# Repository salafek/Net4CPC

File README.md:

# Net4CPC
Net4CPC is an Ethernet interface for the [Amstrad CPC](https://www.cpcwiki.eu/index.php/CPC) range of computers.</br>
It is a stand alone implemetation of the Ethernet interface found on the [Cyboard](https://github.com/salafek/cyboard-for-cpc).</br>
It is supported by [SymbOS](http://symbos.de) and by [KCNet utilities](https://github.com/salafek/KCNet-software-for-Net4CPC) for CP/M.</br> 
</br>

## Notes
The interface has a [Mother X4](https://cpcrulez.fr/hardware-interface-mother_x4.htm) compatible connector.</br> 
The network module is based on the [WIZnet's W5100S](https://www.wiznet.io/product-item/w5100s/) embedded ethernet controller and works in indirect parallel bus mode.</br>
In this mode it needs 4 I/O ports:
- #FD20: MR - Common Register MR
- #FD21: IDM_ARH - Upper 8 bits Offset Address Register
- #FD22: IDM_ARL - Lower 8 bits Offset Address Register
- #FD23: IDM_DR - 8 Bits Data Register

A detailed description on how to program the module, with flow diagrams and programming examples, can be found at the WIZnet's official site:</br>
[W5100S TCP Function](https://docs.wiznet.io/Product/iEthernet/W5100S/Application-Note/tcp)</br>
[W5100S UDP Function](https://docs.wiznet.io/Product/iEthernet/W5100S/Application-Note/udp)</br>
[SOCKET-less Command](https://docs.wiznet.io/Product/iEthernet/W5100S/Application-Note/socket-less-command)</br>

The PCB has provision for 2 differrent types of Ethernet modules:
- A Chinese [W5100S module](https://www.aliexpress.com/w/wholesale-%22W5100S-Network-Module%22-parallel.html?catId=0&initiative_id=SB_20230206005326&SearchText=%22W5100S%20Network%20Module%22%20parallel&spm=a2g0o.productlist.1000002.0) with an integrated 3.3V regulator.</br> 
- The original WIZnet's [W5100S](https://github.com/Wiznet/Hardware-Files-of-WIZnet/tree/master/05_Network_Module/WIZ810SMJ) or [W6100](https://github.com/Wiznet/Hardware-Files-of-WIZnet/tree/master/05_Network_Module/WIZ610MJ) modules.</br> 
## Build info
The schematic and layout were generated with Autodesk EAGLE 9.6.2 free edition</br>

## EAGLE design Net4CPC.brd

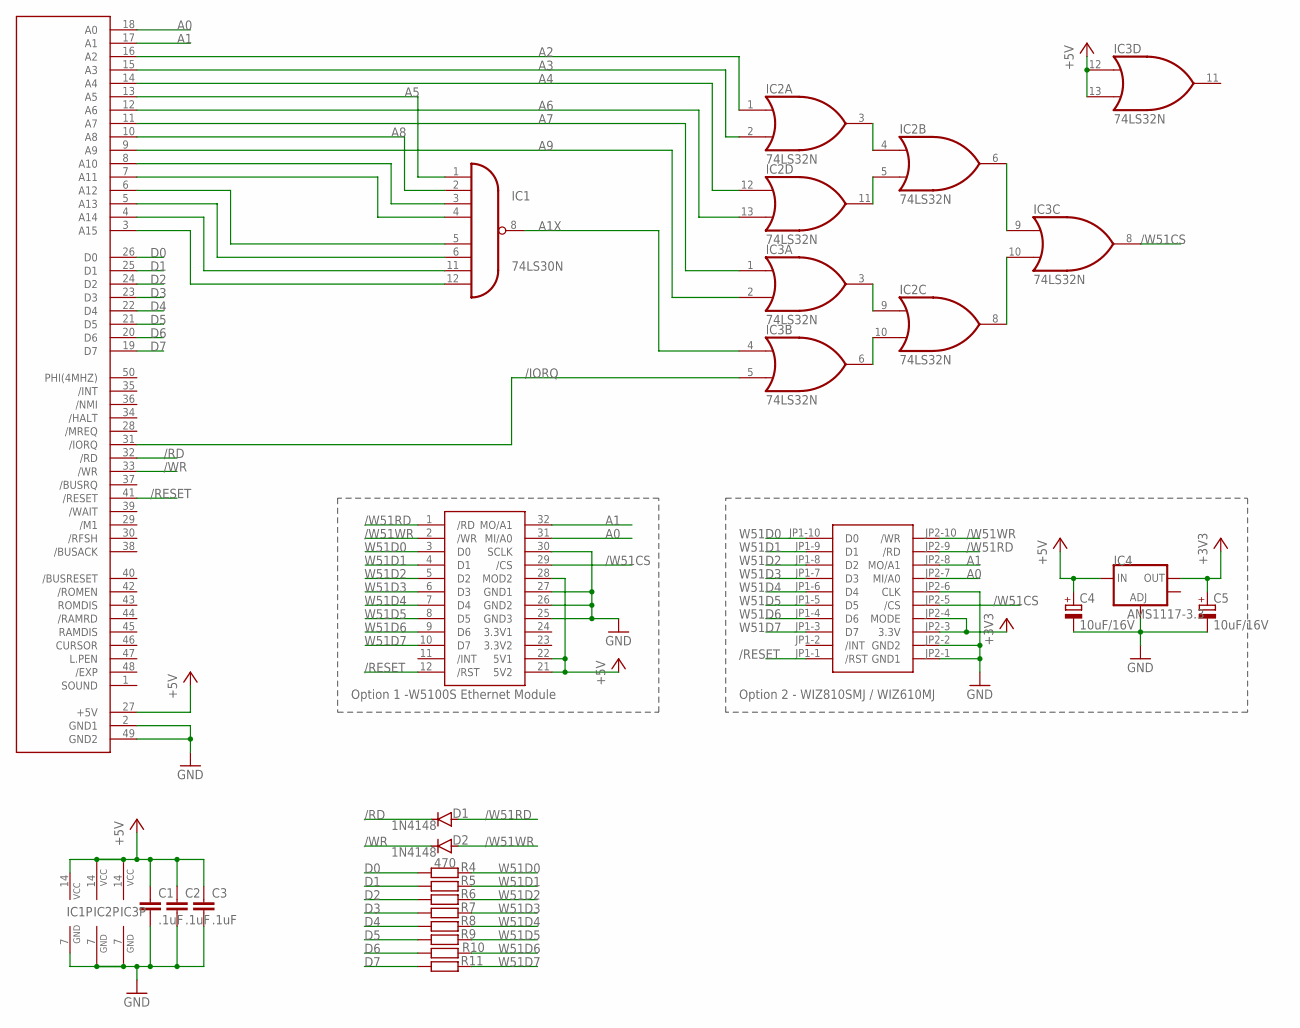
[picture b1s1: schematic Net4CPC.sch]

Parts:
C1, C2, C3: .1uF; C025-025X050
C4, C5: 10uF/16V; E5-6
CON1: CPCBUS; 2X25
D1, D2: 1N4148; DO35-7
IC1: 74LS30N; DIL14
IC2, IC3: 74LS32N; DIL14
IC4: AMS1117-3.3; SOT223
R4, R5, R6, R7, R8, R9, R10, R11: 470; 0204/7
W5100S-MODULE: W5100S-NETWORK-MODULENO-NAMES; W5100S-NETWORK-MODULE-NO-NAMES
WIZ810SMJ: WIZ810SMJ-NETWORK-MODULENO-NAMES; WIZ810SMJ-NETWORK-MODULE-NO-NAMES

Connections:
3.3V1: W5100S-MODULE.24 (3.3V1)
3.3V2: W5100S-MODULE.23 (3.3V2)
+3V3: C5.+, IC4.2 (OUT), WIZ810SMJ.JP2-3 (3.3V), WIZ810SMJ.JP2-4 (MODE)
+5V: C1.1, C2.1, C3.1, C4.+, CON1.27 (+5V), IC1.14 (VCC), IC2.14 (VCC), IC3.12 (I0), IC3.13 (I1), IC3.14 (VCC), IC4.3 (IN), W5100S-MODULE.21 (5V2), W5100S-MODULE.22 (5V1), W5100S-MODULE.28 (MOD2)
/IORQ: CON1.31 (/IORQ), IC3.5 (I1)
/RD: CON1.32 (/RD), D1.C
/RESET: CON1.41 (/RESET), W5100S-MODULE.12 (/RST), WIZ810SMJ.JP1-1 (/RST)
/W51CS: IC3.8 (O), W5100S-MODULE.29 (/CS), WIZ810SMJ.JP2-5 (/CS)
/W51RD: D1.A, W5100S-MODULE.1 (/RD), WIZ810SMJ.JP2-9 (/RD)
/W51WR: D2.A, W5100S-MODULE.2 (/WR), WIZ810SMJ.JP2-10 (/WR)
/WR: CON1.33 (/WR), D2.C
A0: CON1.18 (A0), W5100S-MODULE.31 (MI/A0), WIZ810SMJ.JP2-7 (MI/A0)
A1: CON1.17 (A1), W5100S-MODULE.32 (MO/A1), WIZ810SMJ.JP2-8 (MO/A1)
A1X: IC1.8 (O), IC3.4 (I0)
A2: CON1.16 (A2), IC2.1 (I0)
A3: CON1.15 (A3), IC2.2 (I1)
A4: CON1.14 (A4), IC2.12 (I0)
A5: CON1.13 (A5), IC1.1 (I0)
A6: CON1.12 (A6), IC2.13 (I1)
A7: CON1.11 (A7), IC3.1 (I0)
A8: CON1.10 (A8), IC1.2 (I1)
A9: CON1.9 (A9), IC3.2 (I1)
A10: CON1.8 (A10), IC1.3 (I2)
A11: CON1.7 (A11), IC1.4 (I3)
A12: CON1.6 (A12), IC1.5 (I4)
A13: CON1.5 (A13), IC1.6 (I5)
D0: CON1.26 (D0), R4.1
D1: CON1.25 (D1), R5.1
D2: CON1.24 (D2), R6.1
D3: CON1.23 (D3), R7.1
D4: CON1.22 (D4), R8.1
D5: CON1.21 (D5), R9.1
D6: CON1.20 (D6), R10.1
D7: CON1.19 (D7), R11.1
GND: C1.2, C2.2, C3.2, C4.-, C5.-, CON1.2 (GND1), CON1.49 (GND2), IC1.7 (GND), IC2.7 (GND), IC3.7 (GND), IC4.1 (ADJ), W5100S-MODULE.25 (GND3), W5100S-MODULE.26 (GND2), W5100S-MODULE.27 (GND1), W5100S-MODULE.30 (SCLK), WIZ810SMJ.JP2-1 (GND1), WIZ810SMJ.JP2-2 (GND2), WIZ810SMJ.JP2-6 (CLK)
unnamed: CON1.3 (A15), IC1.12 (I7)
unnamed: CON1.4 (A14), IC1.11 (I6)
unnamed: IC2.3 (O), IC2.4 (I0)
unnamed: IC2.5 (I1), IC2.11 (O)
unnamed: IC2.9 (I0), IC3.3 (O)
unnamed: IC2.10 (I1), IC3.6 (O)
unnamed: IC2.6 (O), IC3.9 (I0)
unnamed: IC2.8 (O), IC3.10 (I1)
W51D0: R4.2, W5100S-MODULE.3 (D0), WIZ810SMJ.JP1-10 (D0)
W51D1: R5.2, W5100S-MODULE.4 (D1), WIZ810SMJ.JP1-9 (D1)
W51D2: R6.2, W5100S-MODULE.5 (D2), WIZ810SMJ.JP1-8 (D2)
W51D3: R7.2, W5100S-MODULE.6 (D3), WIZ810SMJ.JP1-7 (D3)
W51D4: R8.2, W5100S-MODULE.7 (D4), WIZ810SMJ.JP1-6 (D4)
W51D5: R9.2, W5100S-MODULE.8 (D5), WIZ810SMJ.JP1-5 (D5)
W51D6: R10.2, W5100S-MODULE.9 (D6), WIZ810SMJ.JP1-4 (D6)
W51D7: R11.2, W5100S-MODULE.10 (D7), WIZ810SMJ.JP1-3 (D7)

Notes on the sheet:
Option 1 -W5100S Ethernet Module
Option 2 - WIZ810SMJ / WIZ610MJ

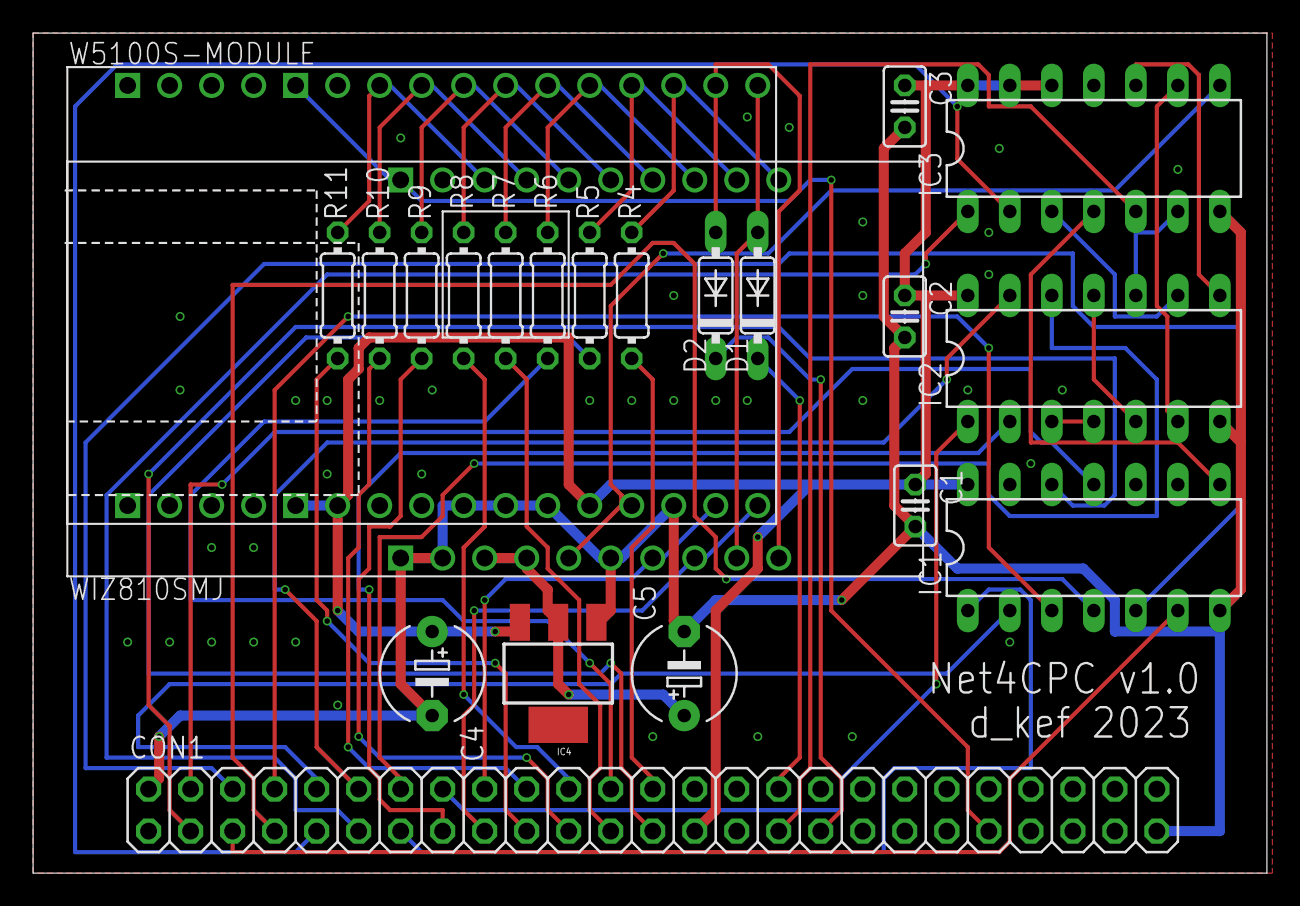
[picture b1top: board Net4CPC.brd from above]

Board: 2 copper layers, 74.6 x 50.8 mm, 22 parts (0 on the bottom side), 49 nets.

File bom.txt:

Partlist

Part          Value                 Package               Digi-Key PN

C1            .1uF                  C025/C320             399-9871-1-ND
C2            .1uF                  C025/C320             399-9871-1-ND
C3            .1uF                  C025/C320             399-9871-1-ND
C4            1uF/16V               E5-06                 B41827A4105M-ND
C5            1uF/16V               E5-06                 B41827A4105M-ND
CON1          CPCBUS                HEADER R/A 50POS      732-5414-ND
D1            1N4148                DO35-7                2368-1N4148-ND
D2            1N4148                DO35-7                2368-1N4148-ND
IC1           74LS30N               DIL14                 296-3693-5-ND
IC2           74LS32N               DIL14                 296-1658-5-ND
IC3           74LS32N               DIL14                 296-1658-5-ND
IC4           AMS1117-3.3           SOT-223               4518-AMS1117-3.3TR-ND
R4            470                   0204/0207             MFR-25FRF52-470R-ND
R5            470                   0204/0207             MFR-25FRF52-470R-ND
R6            470                   0204/0207             MFR-25FRF52-470R-ND
R7            470                   0204/0207             MFR-25FRF52-470R-ND
R8            470                   0204/0207             MFR-25FRF52-470R-ND
R9            470                   0204/0207             MFR-25FRF52-470R-ND
R10           470                   0204/0207             MFR-25FRF52-470R-ND
R11           470                   0204/0207             MFR-25FRF52-470R-ND
W5100S-MODULE W5100S-NETWORK-MODULE W5100S-NETWORK-MODULE -
WIZ810SMJ     WIZ810SMJ / WIZ610MJ  WIZ810SMJ / WIZ610MJ  -

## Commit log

2023-03-03 Add files via upload
    Added voltage value to electrolytic caps.
2023-03-03 Add files via upload
    Added voltage value to electrolytic caps
2023-03-03 Add files via upload
    Changed IC1 type
2023-03-03 Add files via upload
    Corrected file names
2023-03-07 Change electrolytic caps value
2023-03-08 Add files via upload
    Electrolytic capacitors value change
2023-05-05 Added extra utilities
    SymbOS network daemon for net4cpc and set code-page utility for CP/M
